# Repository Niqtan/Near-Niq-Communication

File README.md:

# Near-Niq-Communication (NFC Business Card)

## Project Aims
This is a custom NFC busines card I built so that it makes it eaier for people to access my contact info. For example, when im attending networking events or something. Also, it looks kinda cool lol.

P.S. This was a workshop in the hack club jams https://jams.hackclub.com/jam/hacker-card. Shoutout to Hack Club for this!

## PCB

Image 1. Top view of the 

## Layout and Schematic

## BOM
[View the bom](BOM.csv)

## Firmware
Will be flashing the firmware given by Hack Club!

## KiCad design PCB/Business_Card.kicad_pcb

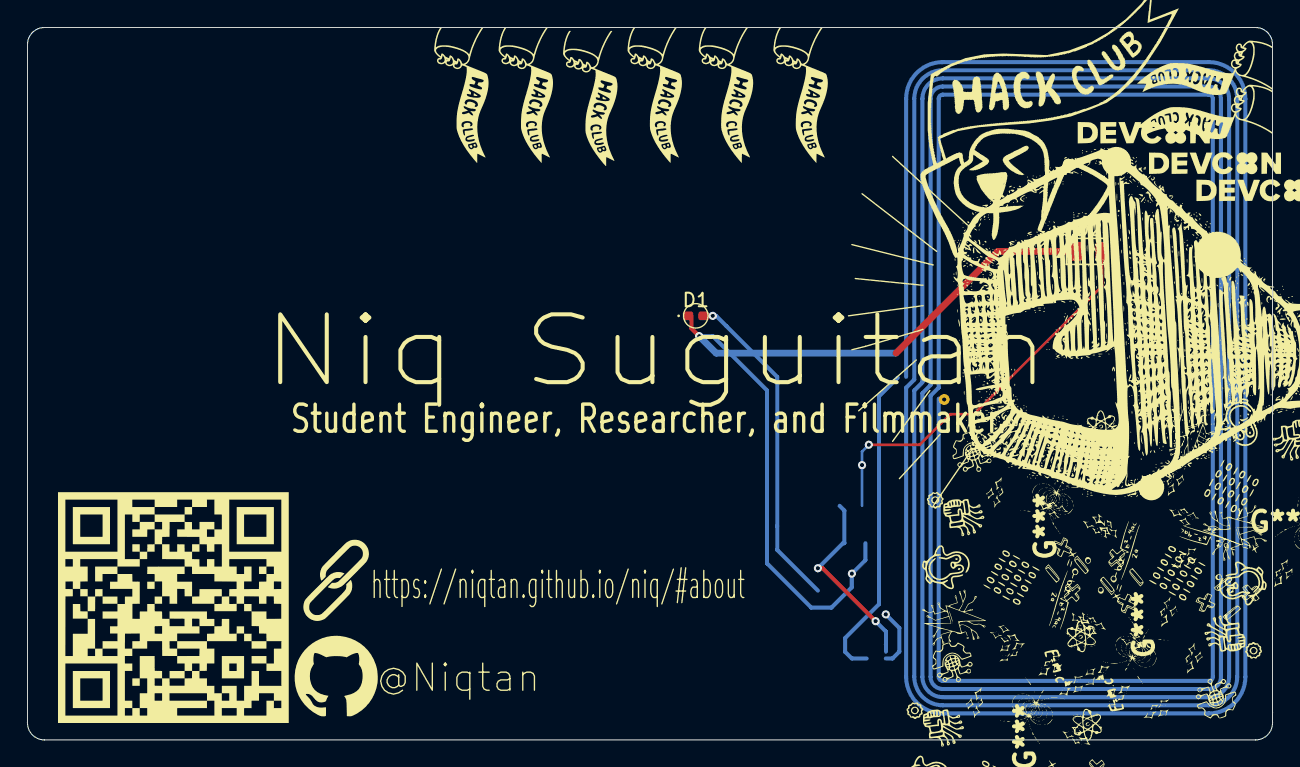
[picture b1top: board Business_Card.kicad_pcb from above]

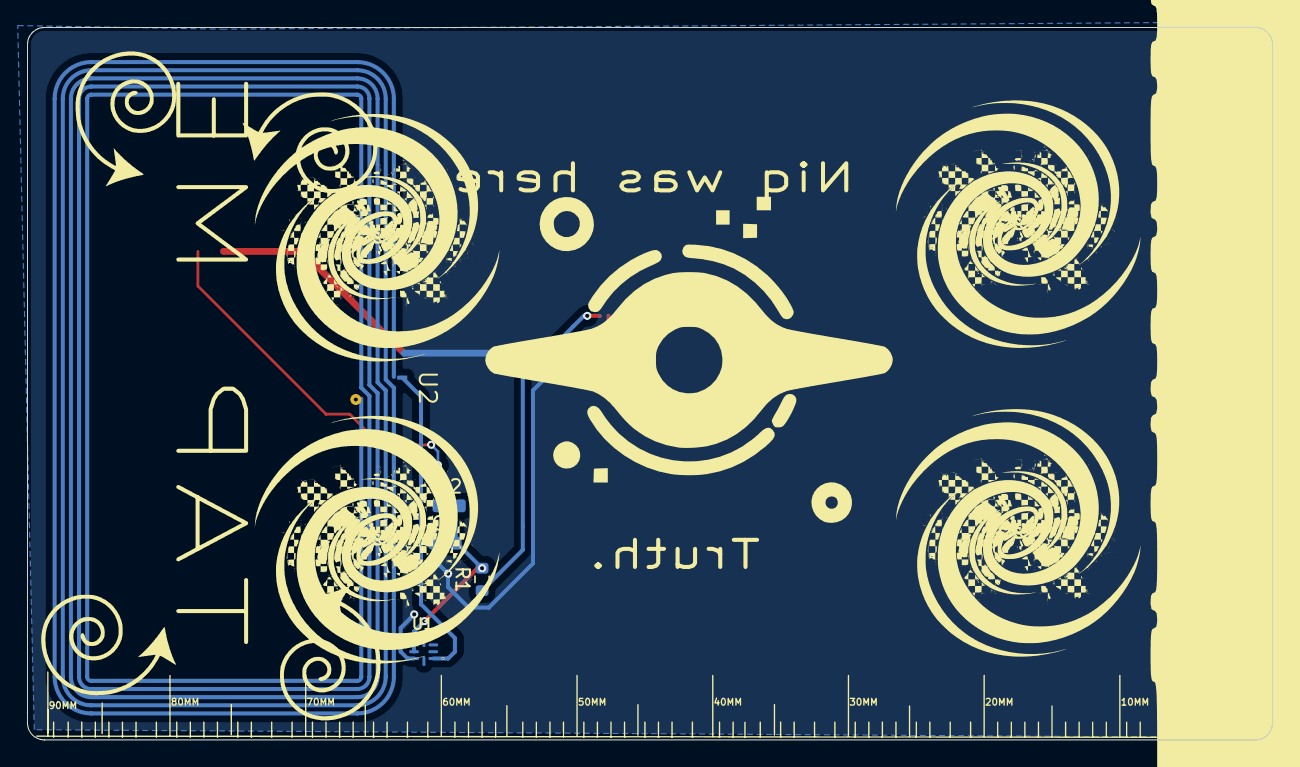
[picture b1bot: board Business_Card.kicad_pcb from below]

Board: 2 copper layers, 91.8 x 52.5 mm, 7 parts (5 on the bottom side), 4 nets.

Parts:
C1: 220nF; C_0603_1608Metric
D1: LG R971-KN-1; LED_0402_1005Metric_Pad0.77x0.64mm_HandSolder
D2: LG R971-KN-1; LED_0805_2012Metric
R1, R2: 100Ω; R_0603_1608Metric
U1: NT3H2111W0FHKH; QFN8P50_160X160X50L40X20N
U2: NFC_ANTENNA; 25X48MM_NFC_ANTENNA

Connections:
GND: C1.2, D1.1 (K), D2.1 (K), U1.2 (VSS)
unnamed: D1.2 (A), R1.1
unnamed: D2.2 (A), R2.1
unnamed: C1.1, R1.2, R2.2, U1.6 (VCC), U1.7 (VOUT)

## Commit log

2025-07-26 new proj
2025-07-26 polish
2025-07-27 updated files
2025-08-01 added pcb
2025-08-02 different art, bom, and changed schematic
2025-08-10 added back art
